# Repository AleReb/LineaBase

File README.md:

# LineaBase
codigos para compartir de base proyecto de multiples estaciones de calidad ambiental

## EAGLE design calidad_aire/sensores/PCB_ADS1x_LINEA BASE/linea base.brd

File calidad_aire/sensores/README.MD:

# Sistema de Monitoreo Ambiental

**Autor:** Alejandro Rebolledo  
**Revisión:** 0.3  
**Fecha:** 30 de julio del 2025

## Descripción general
Este firmware implementa un sistema integrado para monitorear múltiples parámetros ambientales y climáticos utilizando una placa madre Rev. D basada en ESP32. El sistema adquiere datos desde diversos sensores y los almacena localmente en una tarjeta SD, además de enviarlos periódicamente mediante comunicación GSM/LTE al servidor remoto especificado.

## Características principales
- Adquisición de múltiples parámetros ambientales (NO₂, CO, OX, SO₂, partículas PM, CO₂, temperatura, humedad, presión, viento, lluvia, radiación solar, TVOC, UV).
- Almacenamiento en tarjeta SD en formato CSV.
- Envío periódico de datos a servidor remoto usando HTTP y módem SIM7600.
- Captura y transmisión periódica de imágenes desde una cámara externa mediante UART.
- Uso eficiente del watchdog (WDT) para estabilidad operativa.

## Variables medidas y almacenadas en SD
- Timestamp (epoch y fecha/hora humana)
- Batería de estación
- Temperatura de estación
- Calidad de señal
- Valores brutos sensores electroquímicos (NO₂, CO, OX, NO, SO₂)
- Valores ambientales del sensor PMS5003 (PM 10, PM 2.5, temperatura y humedad)
- Valores del sensor CO₂ (interno, raw, custom)
- Parámetros climáticos (temperatura, humedad, presión atmosférica)
- Datos meteorológicos (velocidad y dirección del viento, lluvia acumulada, radiación solar)
- TVOC
- Índice e intensidad UV

## Hardware requerido
- ESP32
- Módulo GSM/LTE SIM7600
- ADS1115 (ADC externo)
- MH-Z19 (sensor CO₂)
- PMS5003 (sensor PM)
- Sensores Modbus (velocidad y dirección del viento, UV)
- Sensores I²C (TVOC, SO₂)
- Tarjeta SD para almacenamiento local
- Cámara UART externa para imágenes

## Librerías requeridas
- TinyGSM
- ArduinoJson
- Adafruit ADS1115
- U8g2
- RTC_DS3231
- ModbusMaster
- MHZ19

## Instalación
1. Clonar este repositorio
```sh
git clone https://github.com/AleReb/LineaBase.git
```
2. Instalar dependencias necesarias desde el gestor de librerías de Arduino IDE.
3. Configurar los parámetros específicos (APN, URLs, intervalos de medición y envío) en el archivo principal del firmware.
4. Cargar el firmware en el ESP32 mediante Arduino IDE o plataforma similar.

## Uso
El sistema opera de manera autónoma una vez encendido. Asegúrese de verificar periódicamente:
- Estado de conexión celular.
- Integridad de los datos almacenados en la tarjeta SD.
- Nivel de batería y calidad de señal.
## Bugs conocidos
El hardware tiene varias limitaciones:
- Estado de conexión celular al ser muy bajo a veces no se puede transmitir la foto.
- El regulador de voltaje no permite la activacion del wifi.
- El cable de la camara tiene que ser lo mas corto posible, hay limitaciones de transmision por serial.

## Soporte y contacto
Para cualquier consulta técnica o reporte de fallos, contactar a Alejandro Rebolledo mediante los canales establecidos en este repositorio o por correo arebolledo@udd.cl.

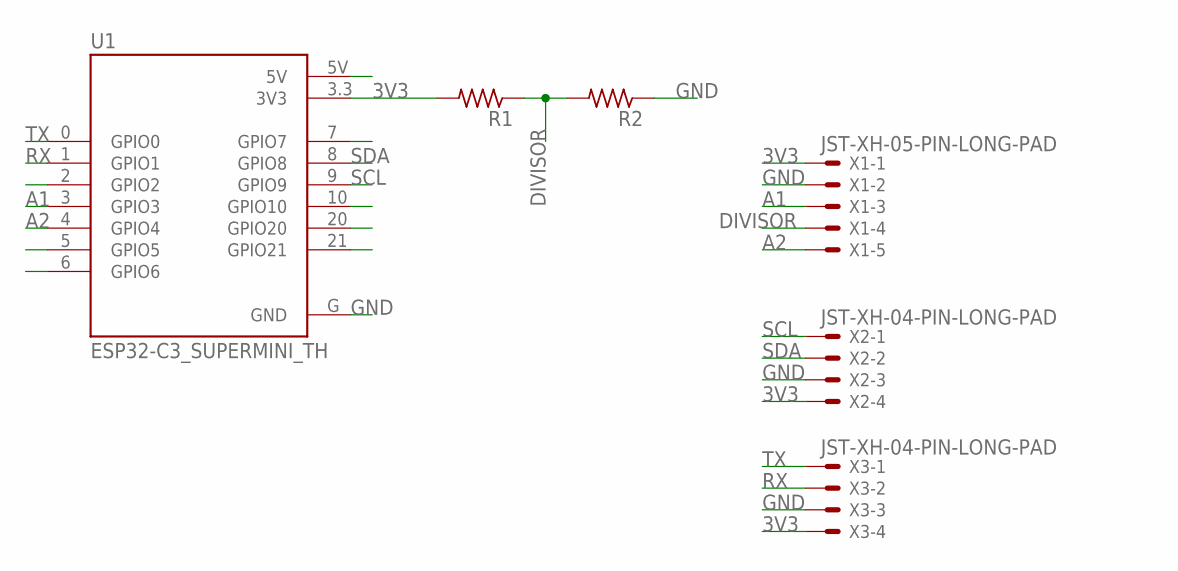
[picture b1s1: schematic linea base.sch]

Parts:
R1, R2: R-US_0204/7; 0204/7
U1: ESP32-C3_SUPERMINI_TH; MODULE_ESP32-C3_SUPERMINI_TH
X1: JST-XH-05-PIN-LONG-PAD; JST-XH-05-PACKAGE-LONG-PAD
X2, X3: JST-XH-04-PIN-LONG-PAD; JST-XH-04-PACKAGE-LONG-PAD

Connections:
3V3: R1.2, U1.3.3 (3V3), X1.1, X2.4, X3.4
A1: U1.3 (GPIO3), X1.3
A2: U1.4 (GPIO4), X1.5
DIVISOR: R1.1, R2.2, X1.4
GND: R2.1, U1.G (GND), X1.2, X2.3, X3.3
RX: U1.1 (GPIO1), X3.2
SCL: U1.9 (GPIO9), X2.1
SDA: U1.8 (GPIO8), X2.2
TX: U1.0 (GPIO0), X3.1

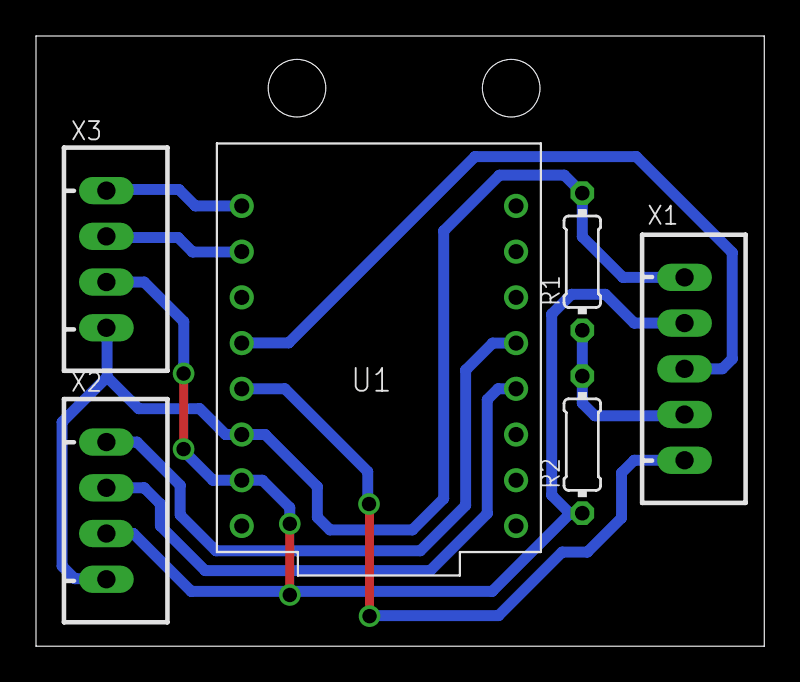
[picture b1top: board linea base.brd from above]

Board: 2 copper layers, 40.5 x 33.9 mm, 6 parts (0 on the bottom side), 9 nets.

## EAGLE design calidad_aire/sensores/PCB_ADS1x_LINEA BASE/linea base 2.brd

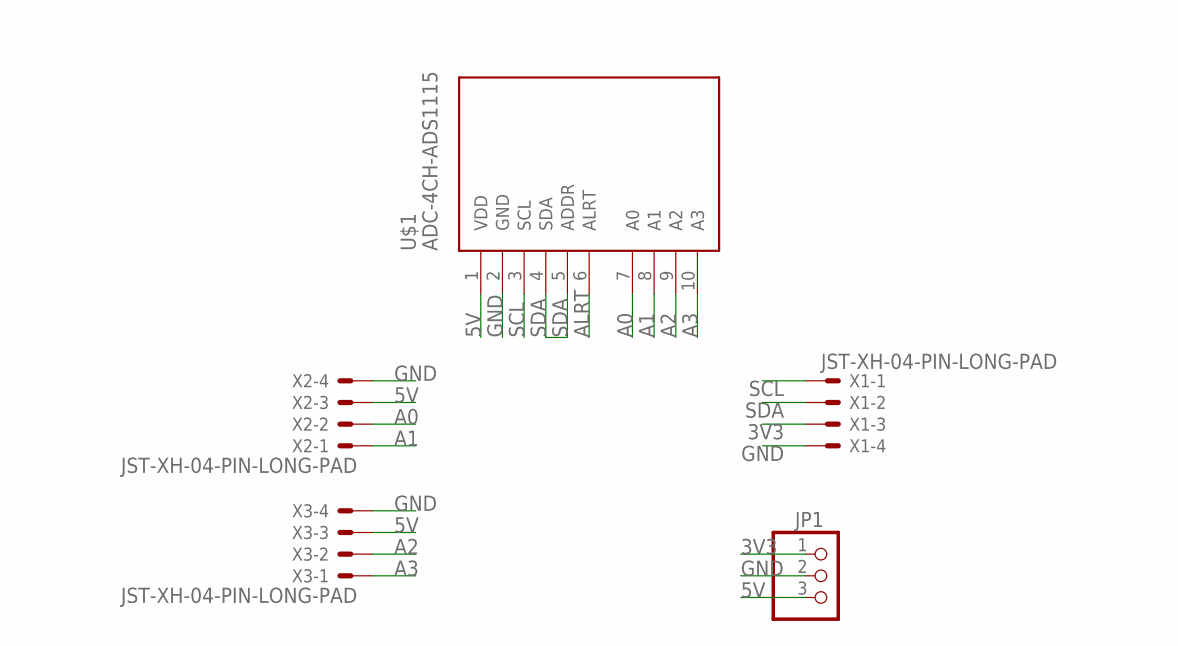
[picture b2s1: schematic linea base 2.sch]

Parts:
JP1: PINHD-1X3; 1X03
U$1: ADC-4CH-ADS1115
X1, X2, X3: JST-XH-04-PIN-LONG-PAD; JST-XH-04-PACKAGE-LONG-PAD

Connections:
3V3: JP1.1, X1.3
5V: JP1.3, U$1.1 (VDD), X2.3, X3.3
A0: U$1.7 (A0), X2.2
A1: U$1.8 (A1), X2.1
A2: U$1.9 (A2), X3.2
A3: U$1.10 (A3), X3.1
ALRT: U$1.6 (ALRT)
GND: JP1.2, U$1.2 (GND), X1.4, X2.4, X3.4
SCL: U$1.3 (SCL), X1.1
SDA: U$1.4 (SDA), U$1.5 (ADDR), X1.2

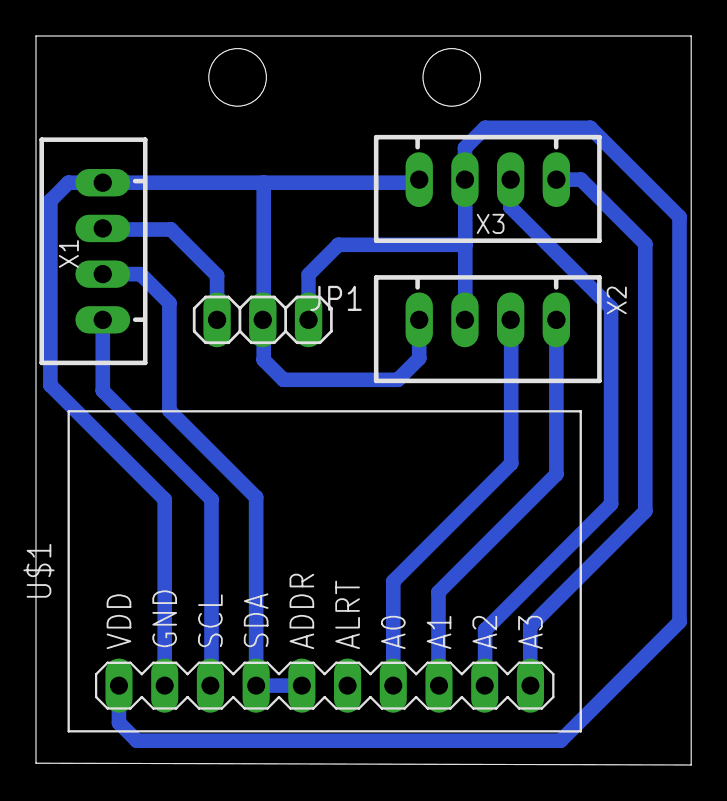
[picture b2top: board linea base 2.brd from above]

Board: 2 copper layers, 36.4 x 40.5 mm, 5 parts (0 on the bottom side), 9 nets.

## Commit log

2025-06-30 codigo hecho por sebastian adonay
    hecho para rescatar datos atlas cientific
2025-06-30 Update and rename Boya_Test/rs485.ino to base_calidad_Agua/Boya_Test/rs485.ino.
2025-07-03 Create estacionmetorologica.ino
    se crea codigo con todos los datos de la miniestacion meteorologica wintop
2025-07-31 Rename README.rm to README.RM
2025-07-31 Rename README.RM to README.MD
2025-08-13 Add files via upload
    actualizado falta limpiar
2025-09-08 Add files via upload
    se sube pcb para ads con sda y adres conectado

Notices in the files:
parts and their libraries:
diy-modules: Released under the Creative Commons Attribution 4.0 International License: http://creativecommons.org/licenses/by/4.0
